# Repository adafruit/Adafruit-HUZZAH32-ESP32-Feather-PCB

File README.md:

## Adafruit HUZZAH32 ESP32 Feather

<a href="http://www.adafruit.com/products/3405"><br/>
Click here to purchase one from the Adafruit shop</a>

PCB files for the Adafruit Feather ESP32 HUZZAH32. Format is EagleCAD schematic and board layout

For more details, check out the product page at
* https://www.adafruit.com/product/3405

### Description

Aww yeah, it's the Feather you have been waiting for! The HUZZAH32 is our ESP32-based Feather, made with the official WROOM32 module. We packed everything you love about Feathers: built in USB-to-Serial converter, automatic bootloader reset, Lithium Ion/Polymer charger, and just about all of the GPIOs brought out so you can use it with any of our Feather Wings. We have other boards in the Feather family, check'em out here.

That module nestled in at the end of this Feather contains a dual-core ESP32 chip, 4 MB of SPI Flash, tuned antenna, and all the passives you need to take advantage of this powerful new processor. The ESP32 has both WiFi and Bluetooth Classic/LE support. That means it's perfect for just about any wireless or Internet-connected project.

Because it's part of our Feather eco-system, you can take advantage of the 50+ Wings that we've designed to add all sorts of cool accessories.

The ESP32 is a perfect upgrade from the ESP8266 that has been so popular. In comparison, the ESP32 has way more GPIO, plenty of analog inputs, two analog outputs, multiple extra peripherals (like a spare UART), two cores so you don't have to yield to the WiFi manager, much higher-speed processor, etc. etc! We think that as the ESP32 gets traction, we'll see more people move to this chip exclusively, as it is so full-featured.

### License

Adafruit invests time and resources providing this open source design, please support Adafruit and open-source hardware by purchasing products from [Adafruit](https://www.adafruit.com)!

Designed by Limor Fried/Ladyada for Adafruit Industries.

Creative Commons Attribution/Share-Alike, all text above must be included in any redistribution. See license.txt for additional details.

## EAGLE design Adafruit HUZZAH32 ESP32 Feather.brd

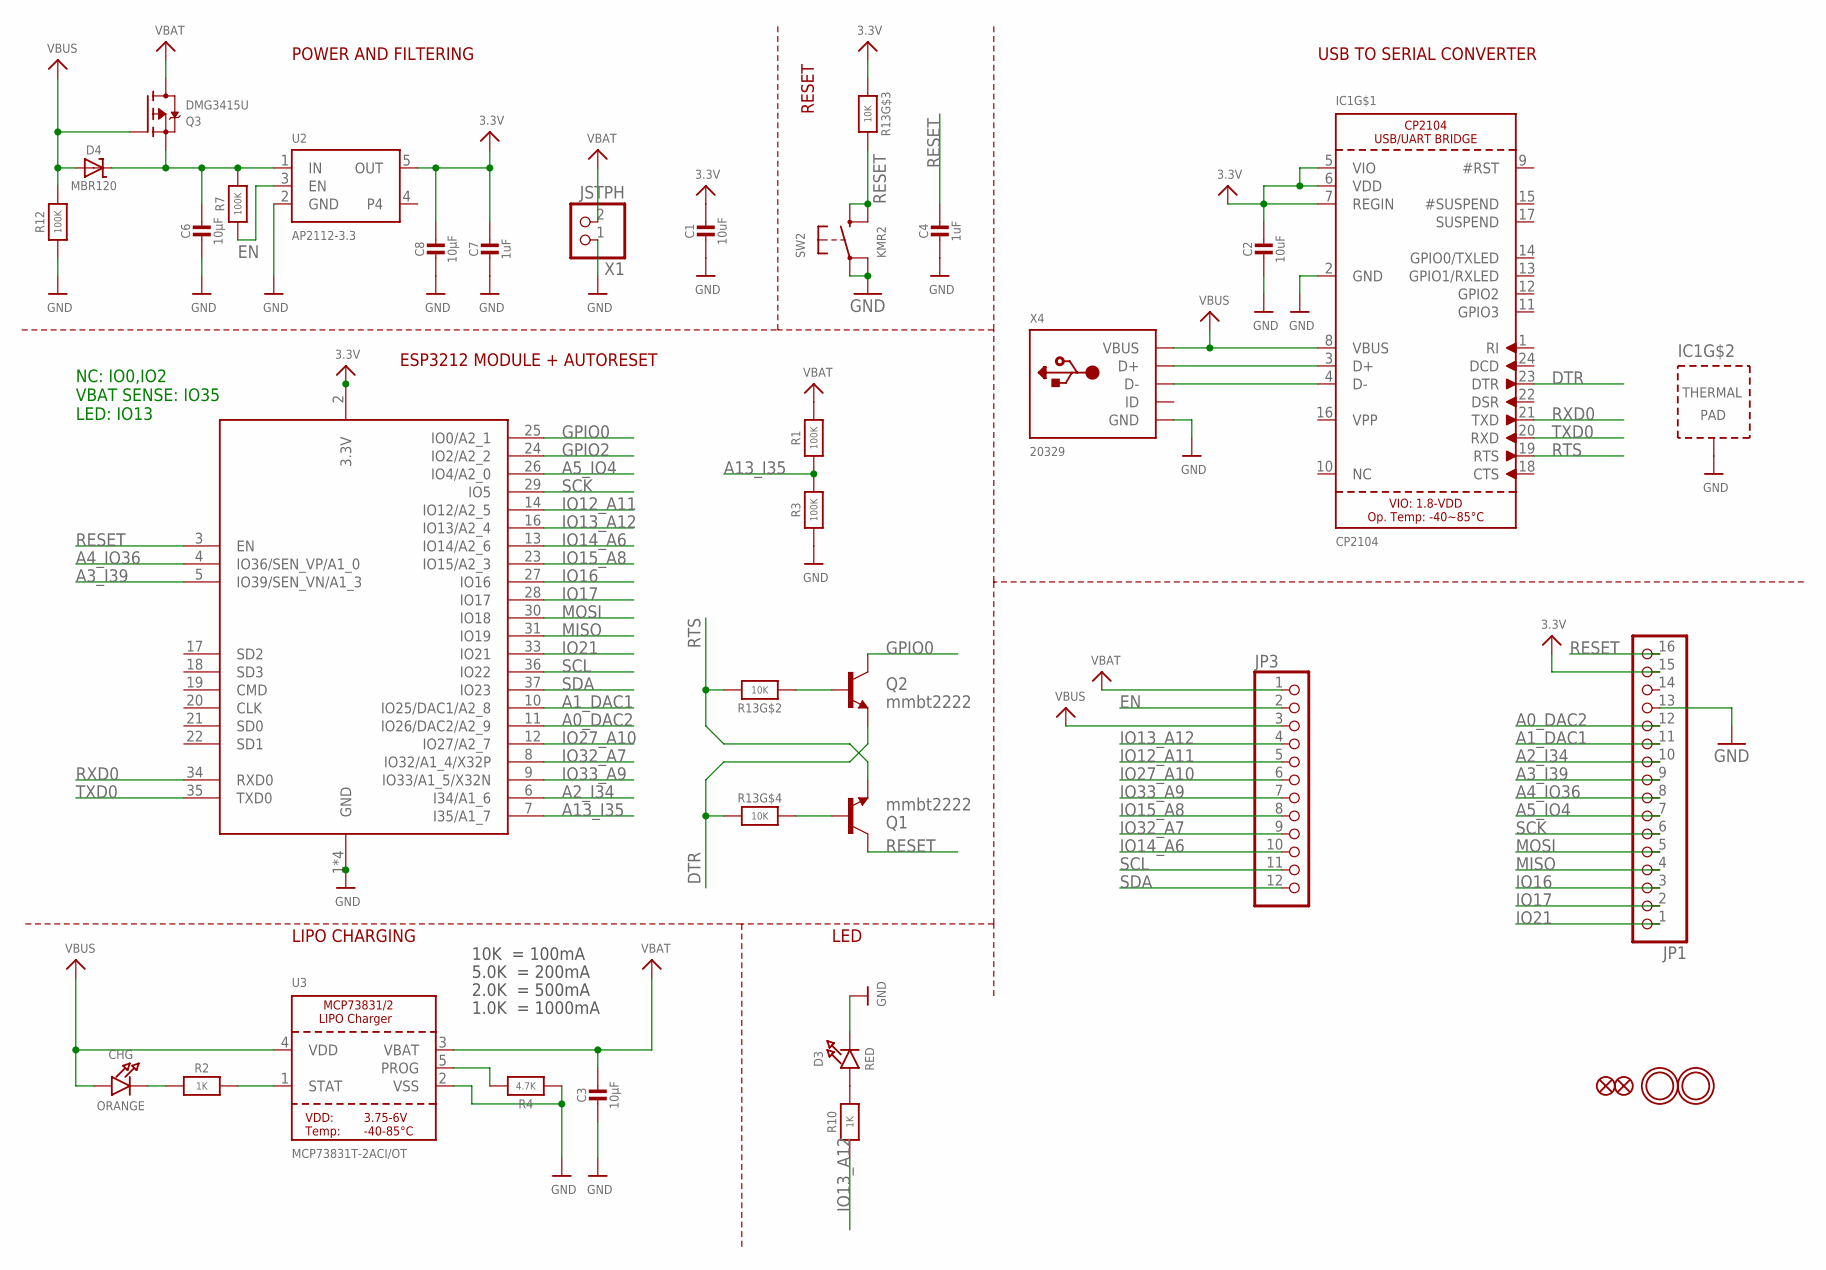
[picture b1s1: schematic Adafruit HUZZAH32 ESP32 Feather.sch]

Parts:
C1, C2: 10uF; 0805-NO
C3, C6, C8: 10µF; 0805-NO
C4, C7: 1uF; 0603-NO
CHG: ORANGE; CHIPLED_0805_NOOUTLINE
D3: RED; CHIPLED_0805_NOOUTLINE
D4: MBR120; SOD-123
IC1: CP2104; QFN24_4MM_SMSC
JP1: HEADER-1X16_MIN; 1X16_ROUND_MIN
JP3: HEADER-1X12_MIN; 1X12_ROUND_MIN
Q1, Q2: mmbt2222; SOT23-3
Q3: DMG3415U; SOT23-R
R1, R3, R7, R12: 100K; 0603-NO
R2, R10: 1K; 0603-NO
R4: 4.7K; 0603-NO
R13: 10K; RESPACK_4X0603
SW2: KMR2; BTN_KMR2_4.6X2.8
U2: AP2112-3.3; SOT23-5
U3: MCP73831T-2ACI/OT; SOT23-5
U$31, U$32: MOUNTINGHOLE2.5; MOUNTINGHOLE_2.5_PLATED
U$34, U$35: FIDUCIAL_1MM
X1: JSTPH; JSTPH2
X2: ESP32_WROOM32_SKINNY; WROOM32_SKINNY
X4: 20329; 4UCONN_20329_V2

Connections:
3.3V: C1.1, C2.1, C7.1, C8.1, IC1.5 (VIO), IC1.6 (VDD), IC1.7 (REGIN), JP1.15, R13.3 (1), U2.5 (OUT), X2.2 (3.3V)
A0_DAC2: JP1.12, X2.11 (IO26/DAC2/A2_9)
A1_DAC1: JP1.11, X2.10 (IO25/DAC1/A2_8)
A2_I34: JP1.10, X2.6 (I34/A1_6)
A3_I39: JP1.9, X2.5 (IO39/SEN_VN/A1_3)
A4_IO36: JP1.8, X2.4 (IO36/SEN_VP/A1_0)
A5_IO4: JP1.7, X2.26 (IO4/A2_0)
A13_I35: R1.1, R3.2, X2.7 (I35/A1_7)
DTR: IC1.23 (DTR), Q2.2 (E), R13.4 (1)
EN: JP3.2, R7.1, U2.3 (EN)
GND: C1.2, C2.2, C3.2, C4.2, C6.2, C7.2, C8.2, D3.C, IC1.2 (GND), IC1.THERM (TP), JP1.13, R3.1, R4.1, R12.1, SW2.A, SW2.A' (P1), U2.2 (GND), U3.2 (VSS), X1.1, X2.1 (GND), X2.15 (GND), X2.38 (GND), X2.P$1 (GND), X4.BASE@1 (GND), X4.BASE@2 (GND), X4.GND, X4.SPRT@1 (GND), X4.SPRT@2 (GND), X4.SPRT@3 (GND), X4.SPRT@4 (GND)
GPIO0: Q2.3 (C), X2.25 (IO0/A2_1)
GPIO2: X2.24 (IO2/A2_2)
IO12_A11: JP3.5, X2.14 (IO12/A2_5)
IO13_A12: JP3.4, R10.1, X2.16 (IO13/A2_4)
IO14_A6: JP3.10, X2.13 (IO14/A2_6)
IO15_A8: JP3.8, X2.23 (IO15/A2_3)
IO16: JP1.3, X2.27 (IO16)
IO17: JP1.2, X2.28 (IO17)
IO21: JP1.1, X2.33 (IO21)
IO27_A10: JP3.6, X2.12 (IO27/A2_7)
IO32_A7: JP3.9, X2.8 (IO32/A1_4/X32P)
IO33_A9: JP3.7, X2.9 (IO33/A1_5/X32N)
MISO: JP1.4, X2.31 (IO19)
MOSI: JP1.5, X2.30 (IO18)
unnamed: CHG.C, R2.1
unnamed: IC1.3 (D+), X4.D+
unnamed: R2.2, U3.1 (STAT)
unnamed: R4.2, U3.5 (PROG)
unnamed: D3.A, R10.2
unnamed: IC1.4 (D-), X4.D-
unnamed: C6.1, D4.C, Q3.2 (S), R7.2, U2.1 (IN)
unnamed: Q1.1 (B), R13.5 (2)
unnamed: Q2.1 (B), R13.2 (1)
RESET: C4.1, JP1.16, Q1.3 (C), R13.6 (2), SW2.B (S), SW2.B' (S1), X2.3 (EN)
RTS: IC1.19 (RTS), Q1.2 (E), R13.7 (2)
RXD0: IC1.21 (TXD), X2.34 (RXD0)
SCK: JP1.6, X2.29 (IO5)
SCL: JP3.11, X2.36 (IO22)
SDA: JP3.12, X2.37 (IO23)
TXD0: IC1.20 (RXD), X2.35 (TXD0)
VBAT: C3.1, JP3.1, Q3.3 (D), R1.2, U3.3 (VBAT), X1.2
VBUS: CHG.A, D4.A, IC1.8 (VBUS), JP3.3, Q3.1 (G), R12.2, U3.4 (VDD), X4.VBUS

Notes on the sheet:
POWER AND FILTERING
RESET
10K = 100mA
5.0K = 200mA
2.0K = 500mA
1.0K = 1000mA
USB TO SERIAL CONVERTER
LIPO CHARGING
LED
ESP3212 MODULE + AUTORESET
NC: IO0,IO2 VBAT SENSE: IO35 LED: IO13

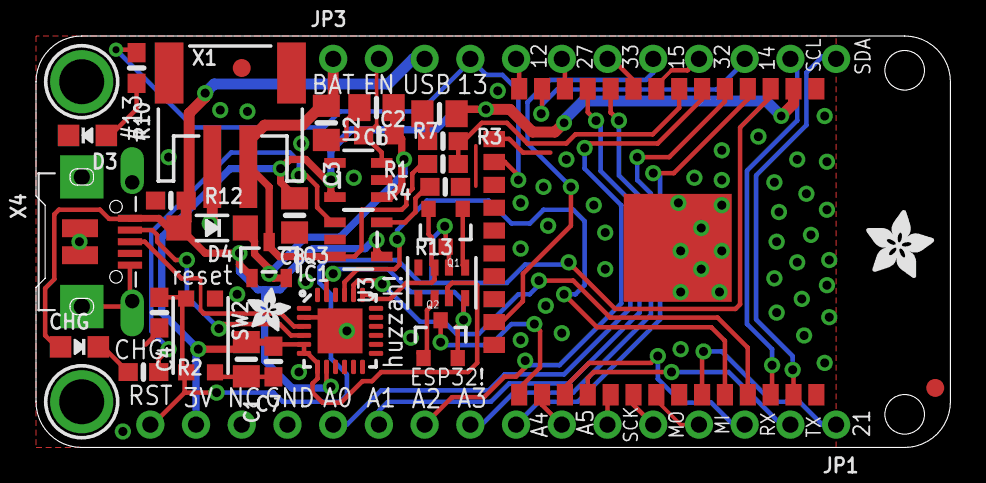
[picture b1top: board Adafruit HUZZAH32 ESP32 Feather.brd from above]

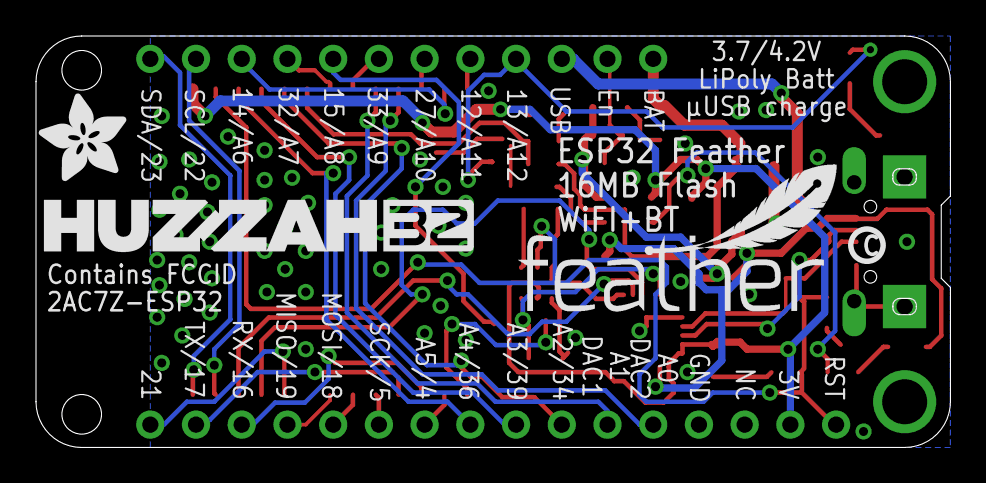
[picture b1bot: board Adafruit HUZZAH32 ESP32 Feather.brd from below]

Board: 2 copper layers, 50.8 x 22.9 mm, 40 parts (4 on the bottom side), 42 nets.

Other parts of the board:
U$7: ADAFRUIT_5MM
U$9: FEATHERLOGO_MED
U$13: PCBFEAT-REV-040
U$14: ADAFRUIT_2.5MM
U$15: ADAFRUIT_3.5MM
U$43: HUZZAH32

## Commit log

2017-05-10 w000t
2022-04-27 Added PrettyPins
2024-11-13 rename pins from IOn to Dn

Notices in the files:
parts and their libraries:
microbuilder: This work is placed in the public domain, and may be freely used for commercial and non-commercial work with the following conditions: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
SparkFun: Licensing: CC v3.0 Share-Alike You are welcome to use this library for commercial purposes.
